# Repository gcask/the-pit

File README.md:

The Pit
=======

Simple arduino-based gamepad to connect custom switches and toggles and easily bind into DCS (uses standard mappings, nothing fancy).

Supports hundreds of switches on a single arduino board.

Relies on [HC165N Parallel-Load Shift Registers](https://www.ti.com/lit/ds/symlink/sn74hc165.pdf?ts=1660549874101), which are inexpensive ICs, to achieve a high number of inputs.

Firmware
--------

Arduino-based program to manage a Sim Pit efficiently.
The code is setup to be able to handle hundreds of inputs over a single Arduino chip, via the use of shift registers and [SPI](https://en.wikipedia.org/wiki/Serial_Peripheral_Interface).

The recommended and target board is [Leonardo](https://docs.arduino.cc/hardware/leonardo).

### Setup

* Download and install [Arduino IDE v2](https://www.arduino.cc/en/software)
* Copy the `firmware/hardware` folder to your local Arduino install, ie `%USERPROFILE%/Documents/Arduino/`.
  - In the end, you should have a `%USERPROFILE%/Documents/Arduino/hardware/thepit/avr/boards.txt` file.
  - You can verify it works if your Arduino can locate a `The Pit (Leonardo)` board.

### Uploading

Because the software is trying to maximize available inputs, it eats up the endpoints that are used to upload a sketch any time.
Reset the board during the `Upload...` phase, otherwise it will fail.

### Customizing

Customizable values, such as the number of daisy-chained hc165, how many gamepads we're emulating, etc, are available in `thepitconfig.user.h`.

Hardware
--------

### Daisy-chained hc165 Board

A simple board to easily daisy-chain several hc165 together.
Each board has 4 connectors:
* 1x daisy chain in, that you connect from the out of the previous board (or from the arduino board)
* 1x daisy chain out, that you connect to the in of the next board (or to the receiving end of the arduino board)
* 2x inputs, each with 4x inputs and 1x ground, that you connect to your switches (pull-up logic, integrated to the board).

### Wiring

Pin 5 is used to latch the hc165, use the ICSP pins for SPI communication.
On the board, the pins from the connector are labeled with their usage:
* Vcc: 5V in
* GND: Ground
* ~PL: Pulse Latch (Pin 5)
* CP: Clock Pulse (SCK, pin 3 on the ICSP)
* DS: Data Serial in (for daisy chain in) (COPI, pin 4 on the ICSP for the first in the chain)
* Q7: Data serial out (for daisy chain out) (CIPO, pin 1 on the ICSP for the last in the chain)

Licenses
--------

Firmware is released under the [Mozilla Public License 2.0](https://mozilla.org/MPL/2.0/)
Hardware designs are Open Hardware, [licensed under CERN-OHL-W v2 or later](https://ohwr.org/cern_ohl_w_v2.txt)

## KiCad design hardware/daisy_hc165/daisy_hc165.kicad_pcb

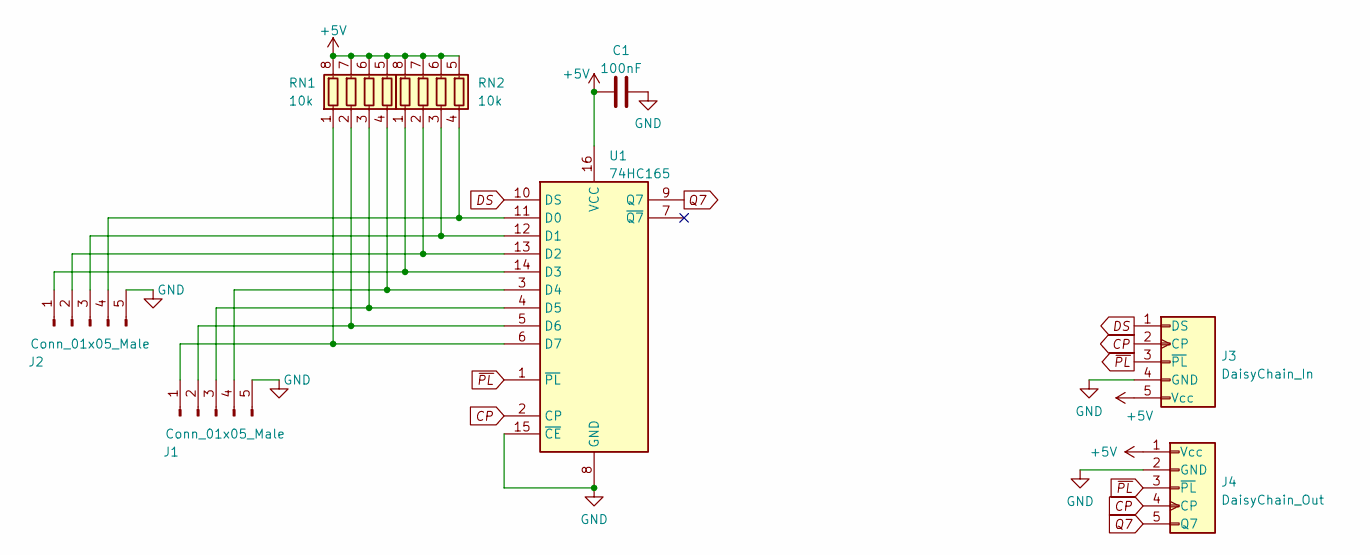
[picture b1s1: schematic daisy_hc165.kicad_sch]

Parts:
C1: 100nF; C_0402_1005Metric; LCSC C1525
J1, J2: Conn_01x05_Male; JST_XH_S5B-XH-A-1_1x05_P2.50mm_Horizontal
J3: DaisyChain_In; JST_XH_S5B-XH-A-1_1x05_P2.50mm_Horizontal
J4: DaisyChain_Out; JST_XH_S5B-XH-A-1_1x05_P2.50mm_Horizontal
RN1, RN2: 10k; R_Array_Convex_4x0603; LCSC C29718
U1: 74HC165; DIP-16_W7.62mm_Socket_LongPads

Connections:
+5V: C1.2, J3.5 (Vcc), J4.1 (Vcc), RN1.5 (R4.2), RN1.6 (R3.2), RN1.7 (R2.2), RN1.8 (R1.2), RN2.5 (R4.2), RN2.6 (R3.2), RN2.7 (R2.2), RN2.8 (R1.2), U1.16 (VCC)
CP: J3.2 (CP), J4.4 (CP), U1.2 (CP)
DS: J3.1 (DS), U1.10 (DS)
GND: C1.1, J1.5, J2.5, J3.4 (GND), J4.2 (GND), U1.8 (GND), U1.15 (~CE)
unnamed: J1.1, RN1.1 (R1.1), U1.6 (D7)
unnamed: J1.2, RN1.2 (R2.1), U1.5 (D6)
unnamed: J1.3, RN1.3 (R3.1), U1.4 (D5)
unnamed: J1.4, RN1.4 (R4.1), U1.3 (D4)
unnamed: J2.1, RN2.1 (R1.1), U1.14 (D3)
unnamed: J2.2, RN2.2 (R2.1), U1.13 (D2)
unnamed: J2.3, RN2.3 (R3.1), U1.12 (D1)
unnamed: J2.4, RN2.4 (R4.1), U1.11 (D0)
Q7: J4.5 (Q7), U1.9 (Q7)
~PL: J3.3 (~PL), J4.3 (~PL), U1.1 (~PL)

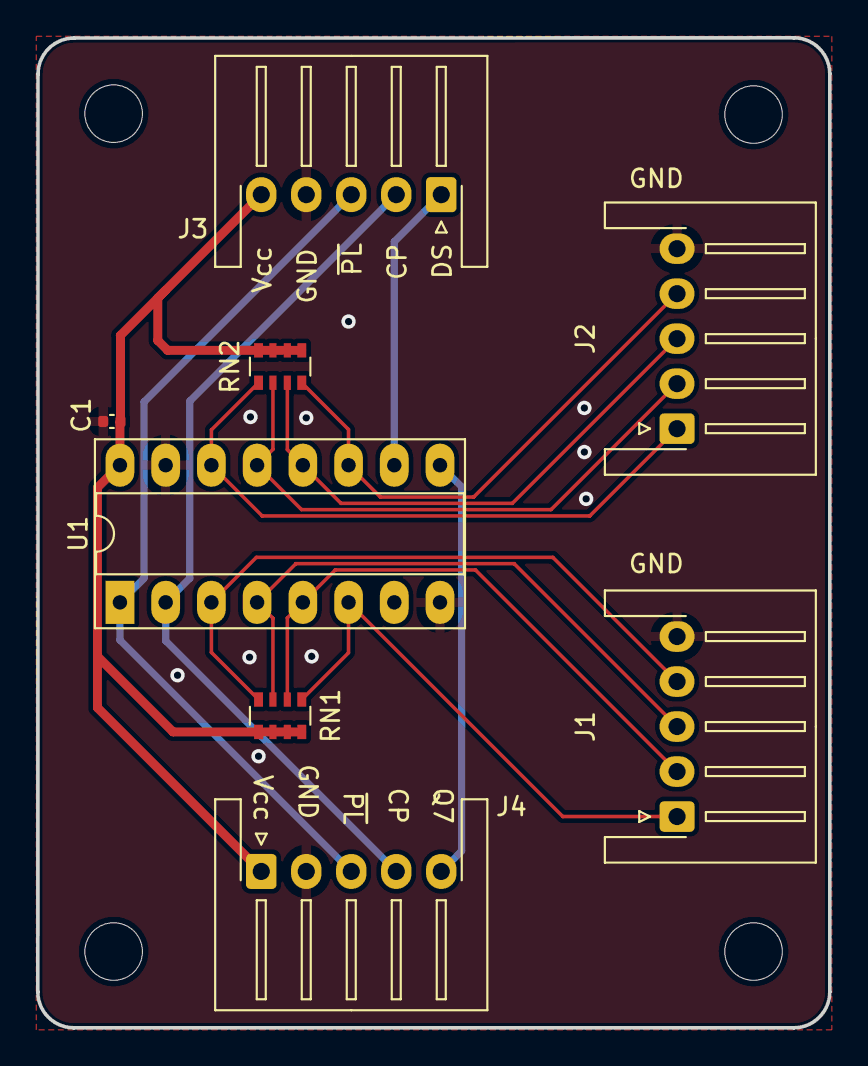
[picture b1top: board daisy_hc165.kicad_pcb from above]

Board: 2 copper layers, 44.0 x 55.0 mm, 8 parts (0 on the bottom side), 14 nets.
